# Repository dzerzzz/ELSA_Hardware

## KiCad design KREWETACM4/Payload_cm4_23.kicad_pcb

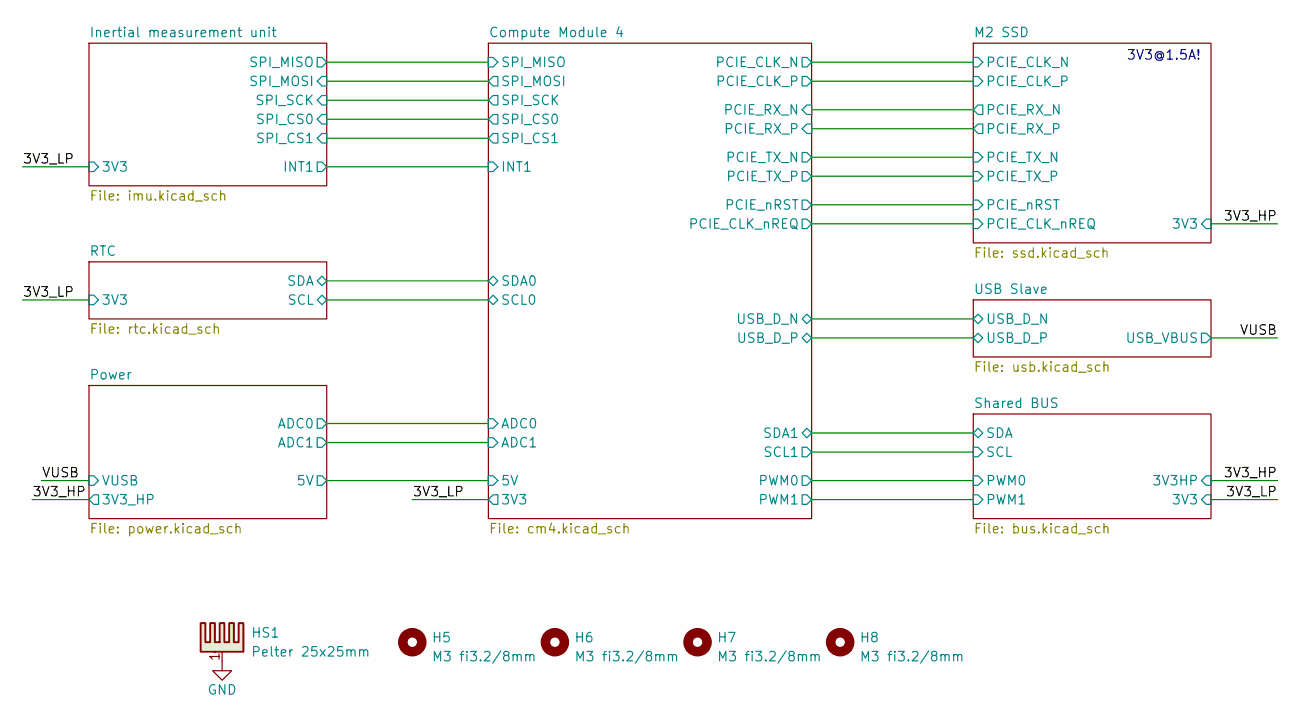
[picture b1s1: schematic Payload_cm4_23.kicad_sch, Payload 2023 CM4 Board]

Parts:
H5, H6, H7, H8: M3 fi3.2/8mm; MountingHole_3.2mm_M3_8mm
HS1: Pelter 25x25mm; Peltier25_25

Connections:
GND: HS1.1; also elsewhere on the board

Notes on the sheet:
3V3@1.5A!

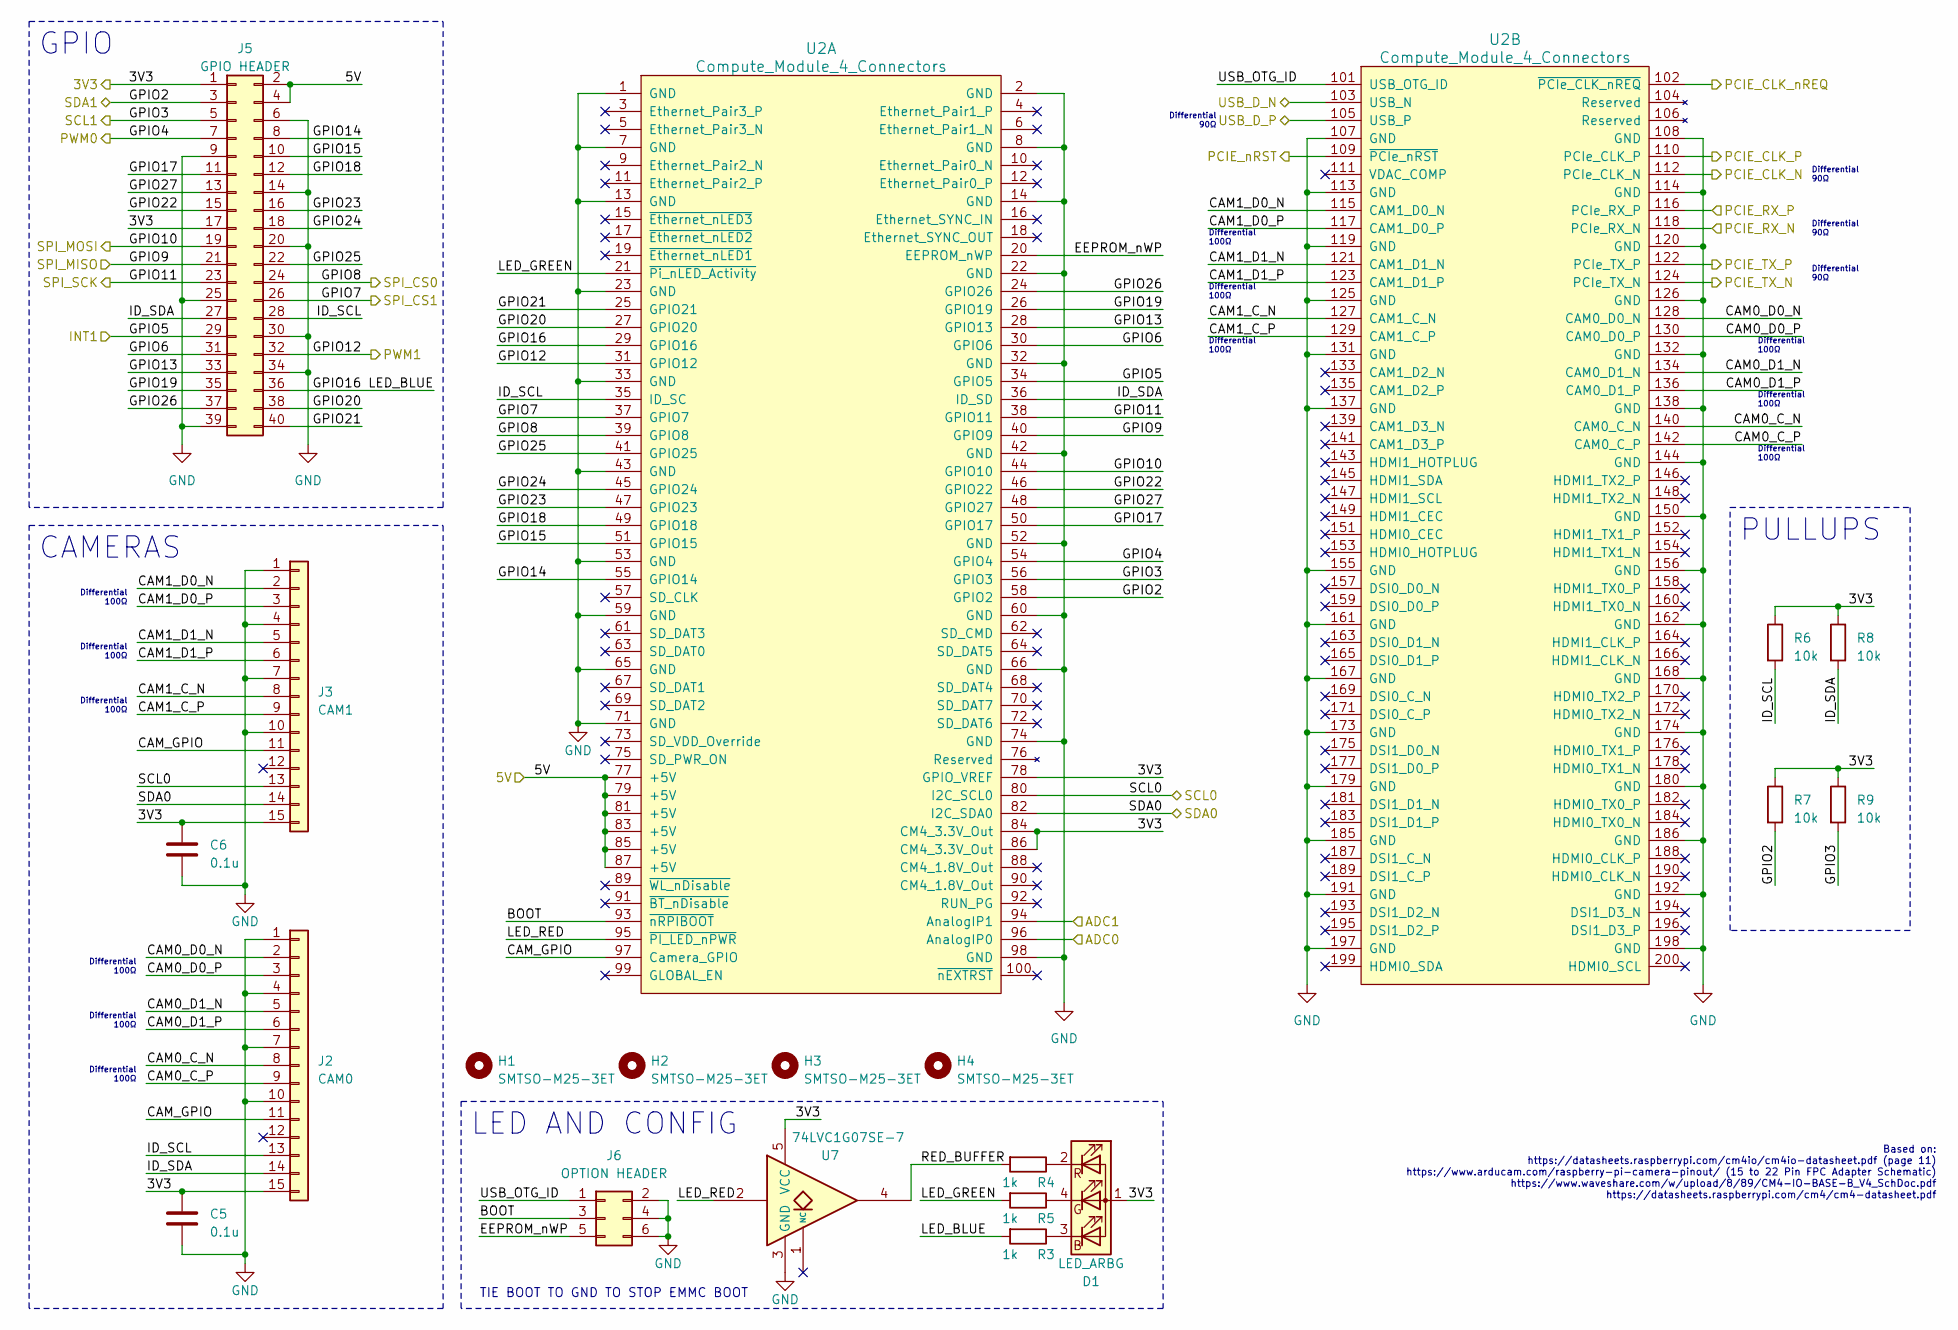
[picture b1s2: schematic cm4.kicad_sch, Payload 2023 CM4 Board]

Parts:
C5, C6: 0.1u; C_0402_1005Metric
D1: LED_ARBG; 150044M155220
H1, H2, H3, H4: SMTSO-M25-3ET; SMTSOM252ET
J2: CAM0; 117342485
J3: CAM1; 117342485
J5: GPIO HEADER; PinHeader_2x20_P2.54mm_Vertical
J6: OPTION HEADER; PinHeader_2x03_P1.27mm_Vertical
R3, R4, R5: 1k; C_0402_1005Metric
R6, R7, R8, R9: 10k; C_0402_1005Metric
U2: Compute_Module_4_Connectors; Raspberry-Pi-4-Compute-Module
U7: 74LVC1G07SE-7; SOT-353_SC-70-5

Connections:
/Compute Module 4/5V: J5.2, J5.4, U2.77 (+5V), U2.79 (+5V), U2.81 (+5V), U2.83 (+5V), U2.85 (+5V), U2.87 (+5V); also elsewhere on the board
/Compute Module 4/ADC0: U2.96 (AnalogIP0); also elsewhere on the board
/Compute Module 4/ADC1: U2.94 (AnalogIP1); also elsewhere on the board
/Compute Module 4/BOOT: J6.3, U2.93 (~nRPIBOOT)
/Compute Module 4/CAM0_C_N: J2.8, U2.140 (CAM0_C_N)
/Compute Module 4/CAM0_C_P: J2.9, U2.142 (CAM0_C_P)
/Compute Module 4/CAM0_D0_N: J2.2, U2.128 (CAM0_D0_N)
/Compute Module 4/CAM0_D0_P: J2.3, U2.130 (CAM0_D0_P)
/Compute Module 4/CAM0_D1_N: J2.5, U2.134 (CAM0_D1_N)
/Compute Module 4/CAM0_D1_P: J2.6, U2.136 (CAM0_D1_P)
/Compute Module 4/CAM1_C_N: J3.8, U2.127 (CAM1_C_N)
/Compute Module 4/CAM1_C_P: J3.9, U2.129 (CAM1_C_P)
/Compute Module 4/CAM1_D0_N: J3.2, U2.115 (CAM1_D0_N)
/Compute Module 4/CAM1_D0_P: J3.3, U2.117 (CAM1_D0_P)
/Compute Module 4/CAM1_D1_N: J3.5, U2.121 (CAM1_D1_N)
/Compute Module 4/CAM1_D1_P: J3.6, U2.123 (CAM1_D1_P)
/Compute Module 4/CAM_GPIO: J2.11, J3.11, U2.97 (Camera_GPIO)
/Compute Module 4/EEPROM_nWP: J6.5, U2.20 (EEPROM_nWP)
/Compute Module 4/GPIO2: J5.3, R7.2, U2.58 (GPIO2); also elsewhere on the board
/Compute Module 4/GPIO4: J5.7, U2.54 (GPIO4); also elsewhere on the board
/Compute Module 4/GPIO5: J5.29, U2.34 (GPIO5); also elsewhere on the board
/Compute Module 4/GPIO6: J5.31, U2.30 (GPIO6)
/Compute Module 4/GPIO7: J5.26, U2.37 (GPIO7); also elsewhere on the board
/Compute Module 4/GPIO8: J5.24, U2.39 (GPIO8); also elsewhere on the board
/Compute Module 4/GPIO9: J5.21, U2.40 (GPIO9); also elsewhere on the board
/Compute Module 4/GPIO10: J5.19, U2.44 (GPIO10); also elsewhere on the board
/Compute Module 4/GPIO11: J5.23, U2.38 (GPIO11); also elsewhere on the board
/Compute Module 4/GPIO12: J5.32, U2.31 (GPIO12); also elsewhere on the board
/Compute Module 4/GPIO13: J5.33, U2.28 (GPIO13)
/Compute Module 4/GPIO14: J5.8, U2.55 (GPIO14)
/Compute Module 4/GPIO15: J5.10, U2.51 (GPIO15)
/Compute Module 4/GPIO16: J5.36, R3.2, U2.29 (GPIO16)
/Compute Module 4/GPIO17: J5.11, U2.50 (GPIO17)
/Compute Module 4/GPIO18: J5.12, U2.49 (GPIO18)
/Compute Module 4/GPIO19: J5.35, U2.26 (GPIO19)
/Compute Module 4/GPIO20: J5.38, U2.27 (GPIO20)
/Compute Module 4/GPIO21: J5.40, U2.25 (GPIO21)
/Compute Module 4/GPIO22: J5.15, U2.46 (GPIO22)
/Compute Module 4/GPIO23: J5.16, U2.47 (GPIO23)
/Compute Module 4/GPIO24: J5.18, U2.45 (GPIO24)
/Compute Module 4/GPIO25: J5.22, U2.41 (GPIO25)
/Compute Module 4/GPIO26: J5.37, U2.24 (GPIO26)
/Compute Module 4/GPIO27: J5.13, U2.48 (GPIO27)
/Compute Module 4/ID_SCL: J2.13, J5.28, R6.2, U2.35 (ID_SC)
/Compute Module 4/ID_SDA: J2.14, J5.27, R8.2, U2.36 (ID_SD)
/Compute Module 4/LED_RED: U2.95 (~PI_LED_nPWR), U7.2
/Compute Module 4/RED_BUFFER: R4.2, U7.4
/Compute Module 4/SCL0: J3.13, U2.80 (I2C_SCL0); also elsewhere on the board
/Compute Module 4/SDA0: J3.14, U2.82 (I2C_SDA0); also elsewhere on the board
/Compute Module 4/USB_OTG_ID: J6.1, U2.101 (USB_OTG_ID)
/M2 SSD/PCIE_CLK_N: U2.112 (PCIe_CLK_N); also elsewhere on the board
/M2 SSD/PCIE_CLK_P: U2.110 (PCIe_CLK_P); also elsewhere on the board
/M2 SSD/PCIE_CLK_nREQ: U2.102 (~PCIe_CLK_nREQ); also elsewhere on the board
/M2 SSD/PCIE_RX_N: U2.118 (PCIe_RX_N); also elsewhere on the board
/M2 SSD/PCIE_RX_P: U2.116 (PCIe_RX_P); also elsewhere on the board
/M2 SSD/PCIE_TX_N: U2.124 (PCIe_TX_N); also elsewhere on the board
/M2 SSD/PCIE_TX_P: U2.122 (PCIe_TX_P); also elsewhere on the board
/M2 SSD/PCIE_nRST: U2.109 (~PCIe_nRST); also elsewhere on the board
/USB Slave/USB_D_N: U2.103 (USB_N); also elsewhere on the board
/USB Slave/USB_D_P: U2.105 (USB_P); also elsewhere on the board
GND: C5.2, C6.2, J2.1, J2.4, J2.7, J2.10, J3.1, J3.4, J3.7, J3.10, J5.6, J5.9, J5.14, J5.20, J5.25, J5.30, J5.34, J5.39, J6.2, J6.4, J6.6, U2.1 (GND), U2.2 (GND), U2.7 (GND), U2.8 (GND), U2.13 (GND), U2.14 (GND), U2.22 (GND), U2.23 (GND), U2.32 (GND), U2.33 (GND), U2.42 (GND), U2.43 (GND), U2.52 (GND), U2.53 (GND), U2.59 (GND), U2.60 (GND), U2.65 (GND), U2.66 (GND), U2.71 (GND), U2.74 (GND), U2.98 (GND), U2.107 (GND), U2.108 (GND), U2.113 (GND), U2.114 (GND), U2.119 (GND), U2.120 (GND), U2.125 (GND), U2.126 (GND), U2.131 (GND), U2.132 (GND), U2.137 (GND), U2.138 (GND), U2.144 (GND), U2.150 (GND), U2.155 (GND), U2.156 (GND), U2.161 (GND), U2.162 (GND), U2.167 (GND), U2.168 (GND), U2.173 (GND), U2.174 (GND), U2.179 (GND), U2.180 (GND), U2.185 (GND), U2.186 (GND), U2.191 (GND), U2.192 (GND), U2.197 (GND), U2.198 (GND), U7.3 (GND); also elsewhere on the board
unnamed: D1.3 (BK), R3.1
unnamed: D1.2 (RK), R4.1

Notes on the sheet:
Differential 100Ω
Differential 90Ω
PULLUPS
TIE BOOT TO GND TO STOP EMMC BOOT
LED AND CONFIG
GPIO
CAMERAS
Based on: https://datasheets.raspberrypi.com/cm4io/cm4io-datasheet.pdf (page 11) https://www.arducam.com/raspberry-pi-camera-pinout/ (15 to 22 Pin FPC Adapter Schematic) https://www.waveshare.com/w/upload/8/89/CM4-IO-BASE-B_V4_SchDoc.pdf https://datasheets.raspberrypi.com/cm4/cm4-datasheet.pdf

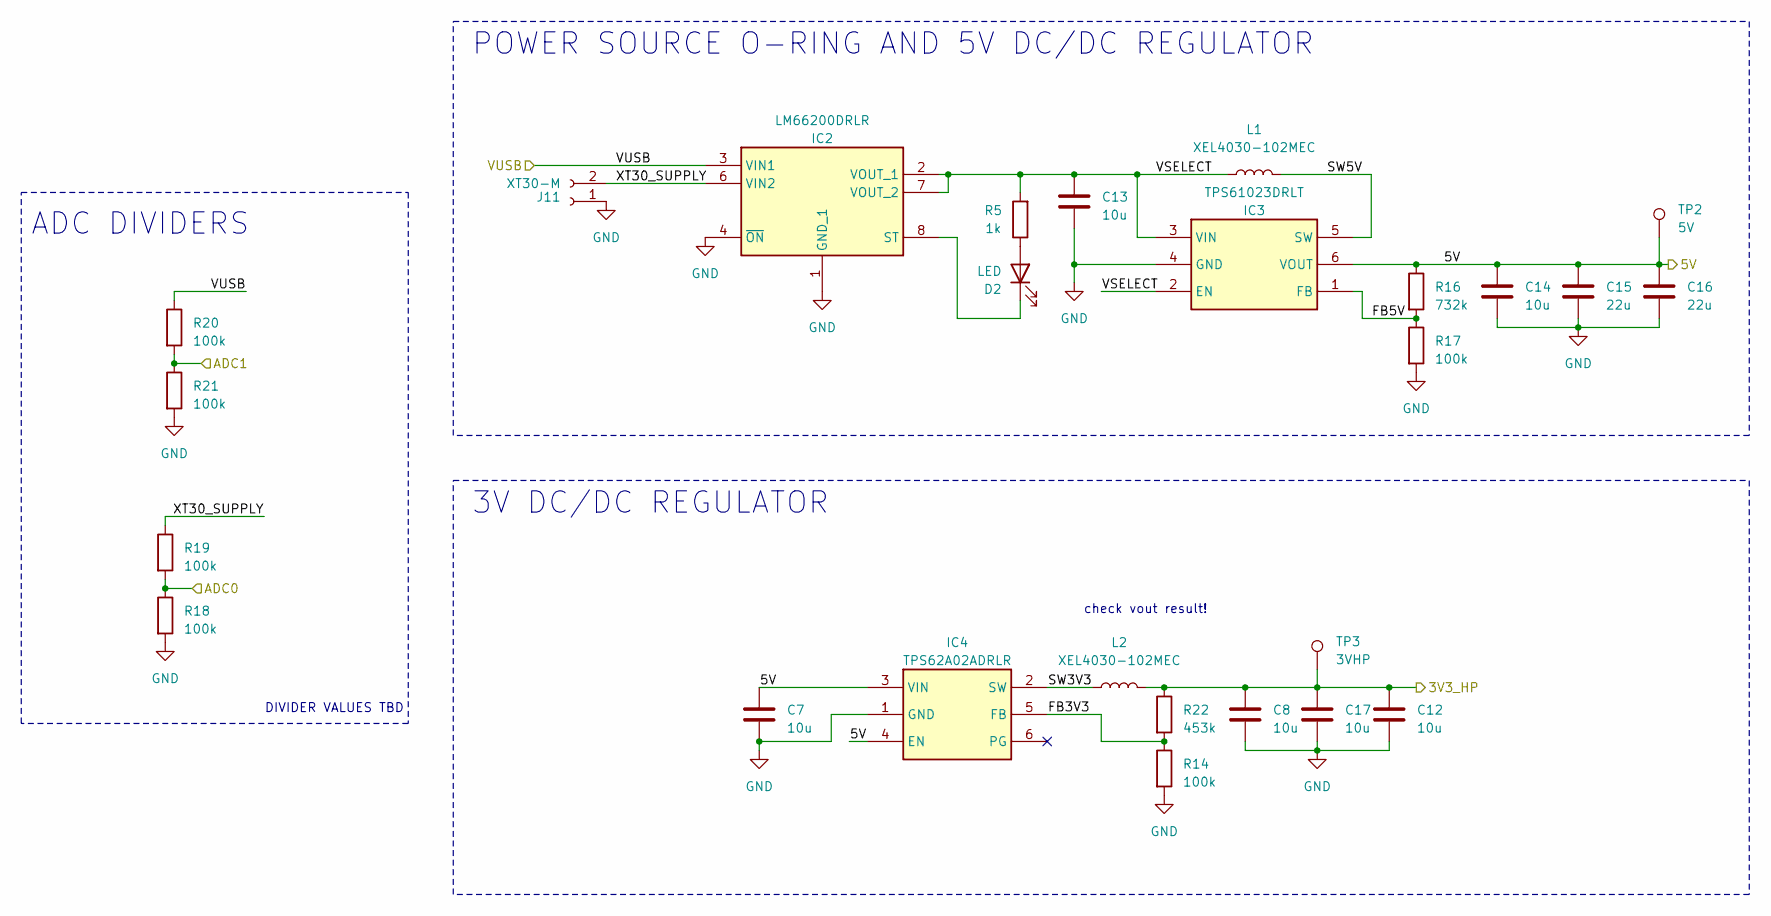
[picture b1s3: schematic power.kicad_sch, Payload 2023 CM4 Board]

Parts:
C7, C8, C12, C13, C14: 10u; C_0805_2012Metric
C15, C16: 22u; C_0805_2012Metric
C17: 10u; C_0402_1005Metric
D2: LED; D_0603_1608Metric
IC2: LM66200DRLR; SOTFL50P160X60-8N; Mouser Part Number 595-LM66200DRLR
IC3: TPS61023DRLT; SOTFL50P160X60-6N; Mouser Part Number 595-TPS61023DRLT
IC4: TPS62A02ADRLR; SOTFL50P160X60-6N; Mouser Part Number 595-TPS62A02ADRLR
J11: XT30-M; AMASS_XT30U-M_1x02_P5.0mm_Vertical
L1, L2: XEL4030-102MEC; L_Coilcraft_XxL4030
R5: 1k; C_0402_1005Metric
R14, R17, R18, R19, R20, R21: 100k; C_0402_1005Metric
R16: 732k; C_0402_1005Metric
R22: 453k; C_0402_1005Metric
TP2: 5V; TestPoint_Pad_D2.0mm
TP3: 3VHP; TestPoint_Pad_D2.0mm

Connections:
/3V3_HP: C8.1, C12.1, C17.1, L2.2, R22.1, TP3.1; also elsewhere on the board
/Compute Module 4/5V: C7.1, C14.1, C15.1, C16.1, IC3.6 (VOUT), IC4.3 (VIN), IC4.4 (EN), R16.1, TP2.1; also elsewhere on the board
/Compute Module 4/ADC0: R18.1, R19.2; also elsewhere on the board
/Compute Module 4/ADC1: R20.2, R21.1; also elsewhere on the board
/Power/FB3V3: IC4.5 (FB), R14.1, R22.2
/Power/FB5V: IC3.1 (FB), R16.2, R17.1
/Power/SW3V3: IC4.2 (SW), L2.1
/Power/SW5V: IC3.5 (SW), L1.2
/Power/XT30_SUPPLY: IC2.6 (VIN2), J11.2, R19.1
/VUSB: IC2.3 (VIN1), R20.1; also elsewhere on the board
GND: C7.2, C8.2, C12.2, C13.2, C14.2, C15.2, C16.2, C17.2, IC2.1 (GND_1), IC2.4 (~ON), IC2.5 (GND_2), IC3.4 (GND), IC4.1 (GND), J11.1, R14.2, R17.2, R18.2, R21.2; also elsewhere on the board
unnamed: D2.1 (K), IC2.8 (ST)

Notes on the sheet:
ADC DIVIDERS
POWER SOURCE O-RING AND 5V DC/DC REGULATOR
check vout result!
3V DC/DC REGULATOR
DIVIDER VALUES TBD

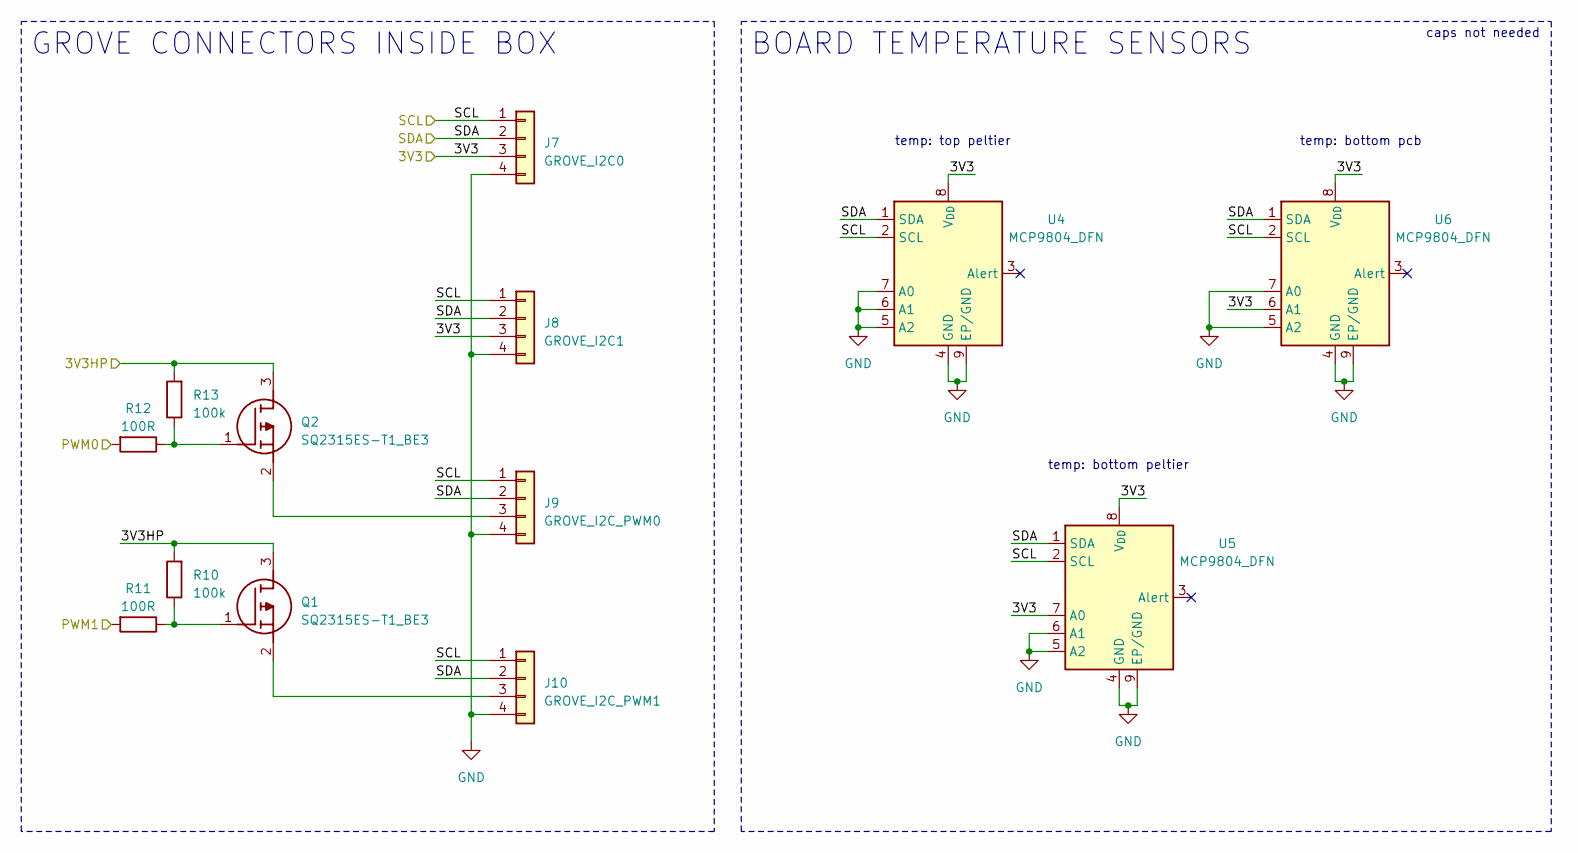
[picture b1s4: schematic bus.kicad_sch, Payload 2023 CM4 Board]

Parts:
J7: GROVE_I2C0; HW4-SMD-2.0
J8: GROVE_I2C1; HW4-SMD-2.0
J9: GROVE_I2C_PWM0; HW4-SMD-2.0
J10: GROVE_I2C_PWM1; HW4-SMD-2.0
Q1, Q2: SQ2315ES-T1_BE3; SOT95P237X112-3N; Mouser Part Number 78-SQ2315ES-T1_BE3
R10, R13: 100k; C_0402_1005Metric
R11, R12: 100R; C_0402_1005Metric
U4, U5, U6: MCP9804_DFN; DFN-8-1EP_3x2mm_P0.5mm_EP1.7x1.4mm

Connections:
/3V3_HP: Q1.3 (D), Q2.3 (D), R10.2, R13.2; also elsewhere on the board
/Compute Module 4/GPIO2: J7.2, J8.2, J9.2, J10.2, U4.1 (SDA), U5.1 (SDA), U6.1 (SDA); also elsewhere on the board
/Compute Module 4/GPIO4: R12.2; also elsewhere on the board
/Compute Module 4/GPIO12: R11.2; also elsewhere on the board
GND: J7.4, J8.4, J9.4, J10.4, U4.4 (GND), U4.5 (A2), U4.6 (A1), U4.7 (A0), U4.9 (EP/GND), U5.4 (GND), U5.5 (A2), U5.6 (A1), U5.9 (EP/GND), U6.4 (GND), U6.5 (A2), U6.7 (A0), U6.9 (EP/GND); also elsewhere on the board
unnamed: J9.3, Q2.2 (S)
unnamed: J10.3, Q1.2 (S)
unnamed: Q1.1 (G), R10.1, R11.1
unnamed: Q2.1 (G), R12.1, R13.1

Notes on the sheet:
temp: bottom pcb
temp: bottom peltier
GROVE CONNECTORS INSIDE BOX
BOARD TEMPERATURE SENSORS
caps not needed
temp: top peltier

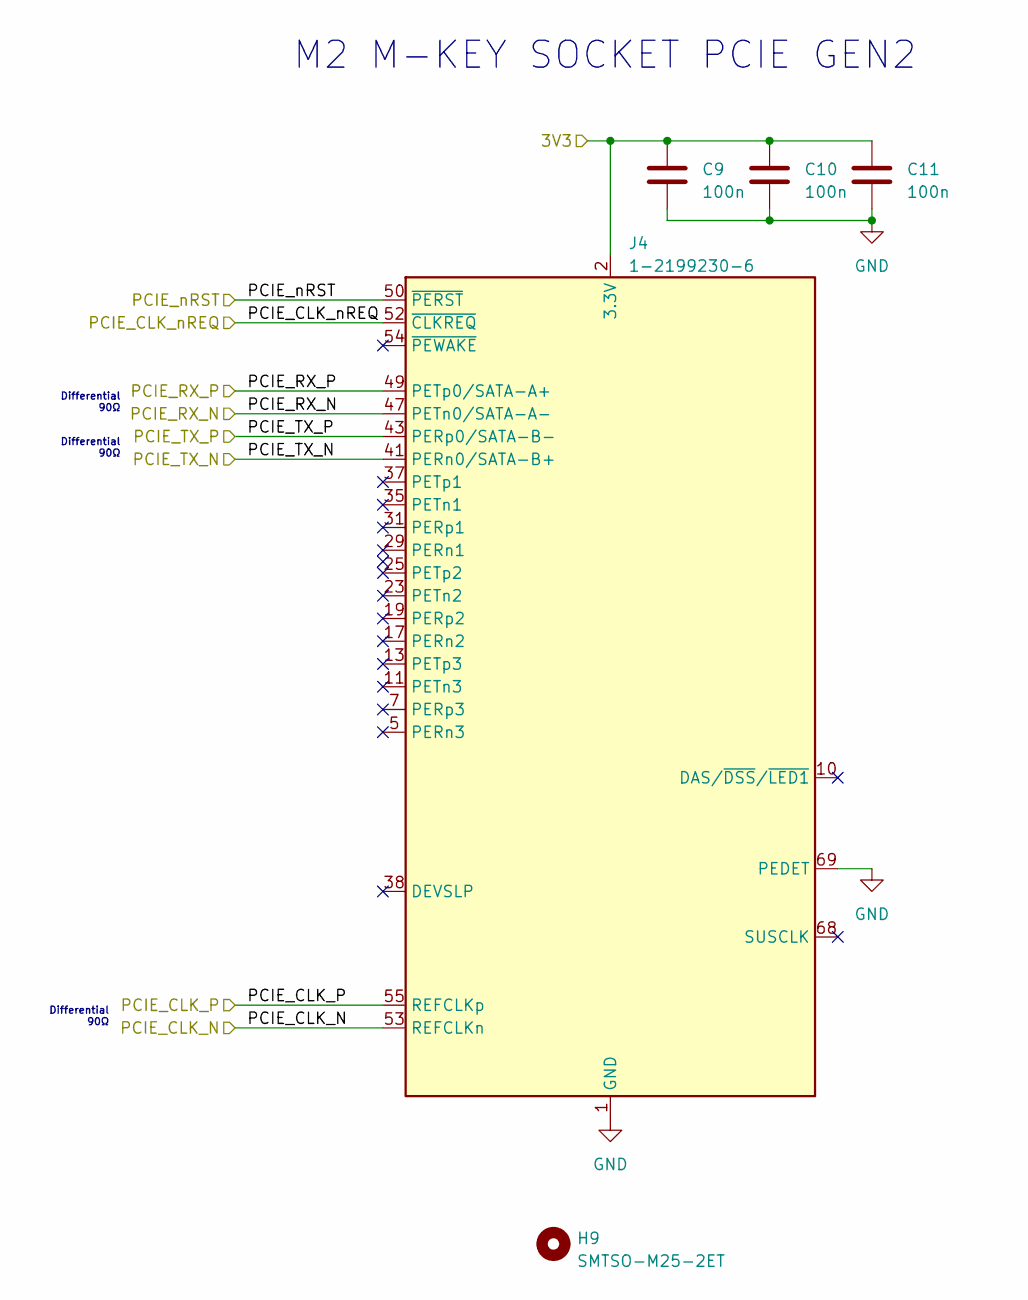
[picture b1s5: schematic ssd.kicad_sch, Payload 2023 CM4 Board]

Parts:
C9, C10, C11: 100n; C_0402_1005Metric
H9: SMTSO-M25-2ET; SMTSOM252ET
J4: 1-2199230-6; 121992306

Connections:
/3V3_HP: C9.1, C10.1, C11.1, J4.2 (3.3V), J4.4 (3.3V), J4.12 (3.3V), J4.14 (3.3V), J4.16 (3.3V), J4.18 (3.3V), J4.70 (3.3V), J4.72 (3.3V), J4.74 (3.3V); also elsewhere on the board
/M2 SSD/PCIE_CLK_N: J4.53 (REFCLKn); also elsewhere on the board
/M2 SSD/PCIE_CLK_P: J4.55 (REFCLKp); also elsewhere on the board
/M2 SSD/PCIE_CLK_nREQ: J4.52 (~CLKREQ); also elsewhere on the board
/M2 SSD/PCIE_RX_N: J4.47 (PETn0/SATA-A-); also elsewhere on the board
/M2 SSD/PCIE_RX_P: J4.49 (PETp0/SATA-A+); also elsewhere on the board
/M2 SSD/PCIE_TX_N: J4.41 (PERn0/SATA-B+); also elsewhere on the board
/M2 SSD/PCIE_TX_P: J4.43 (PERp0/SATA-B-); also elsewhere on the board
/M2 SSD/PCIE_nRST: J4.50 (~PERST); also elsewhere on the board
GND: C9.2, C10.2, C11.2, J4.1 (GND), J4.3 (GND), J4.9 (GND), J4.15 (GND), J4.21 (GND), J4.27 (GND), J4.33 (GND), J4.39 (GND), J4.45 (GND), J4.51 (GND), J4.57 (GND), J4.69 (PEDET), J4.71 (GND), J4.73 (GND), J4.75 (GND); also elsewhere on the board

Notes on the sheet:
Differential 90Ω
M2 M-KEY SOCKET PCIE GEN2

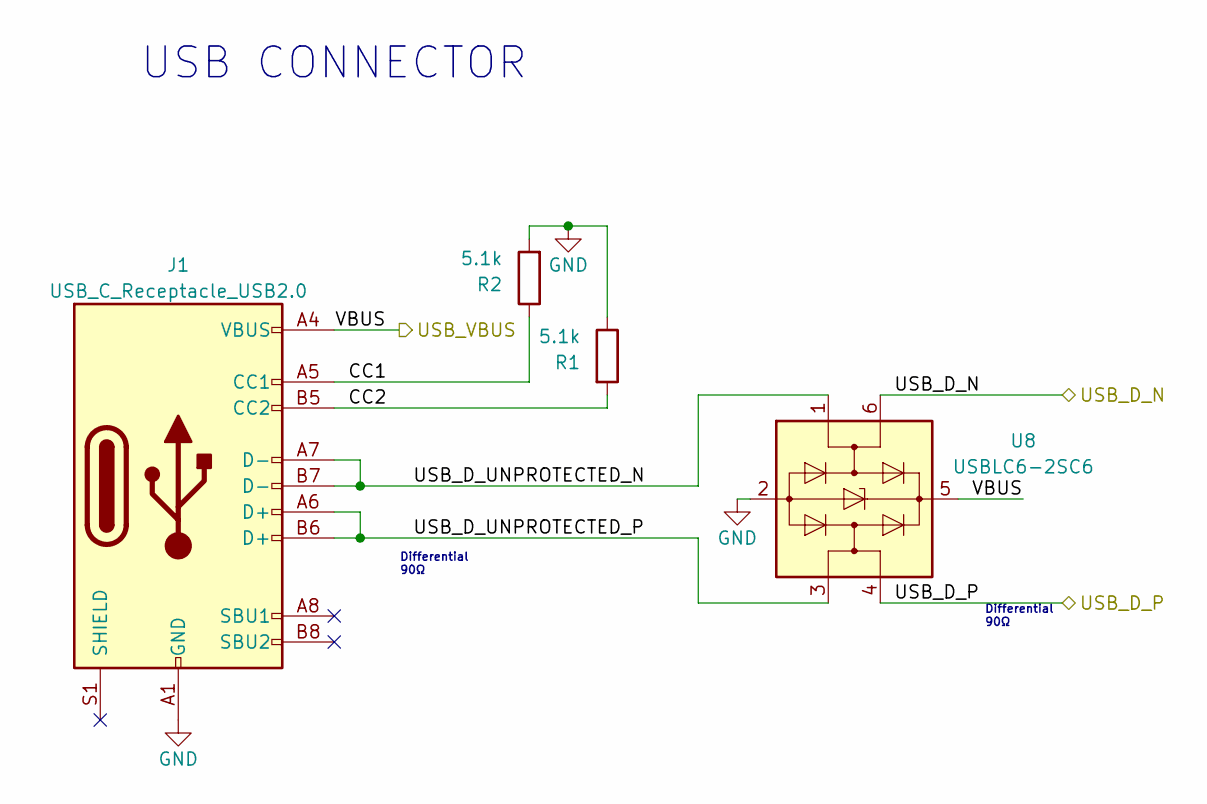
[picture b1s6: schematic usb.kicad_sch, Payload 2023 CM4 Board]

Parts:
J1: USB_C_Receptacle_USB2.0; USB_C_Receptacle_GCT_USB4105-xx-A_16P_TopMnt_Horizontal
R1, R2: 5.1k; C_0402_1005Metric
U8: USBLC6-2SC6; SOT-23-6

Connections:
/USB Slave/CC1: J1.A5 (CC1), R2.1
/USB Slave/CC2: J1.B5 (CC2), R1.2
/USB Slave/USB_D_N: U8.6 (I/O1); also elsewhere on the board
/USB Slave/USB_D_P: U8.4 (I/O2); also elsewhere on the board
/USB Slave/USB_D_UNPROTECTED_N: J1.A7 (D-), J1.B7 (D-), U8.1 (I/O1)
/USB Slave/USB_D_UNPROTECTED_P: J1.A6 (D+), J1.B6 (D+), U8.3 (I/O2)
/VUSB: J1.A4 (VBUS), J1.A9 (VBUS), J1.B4 (VBUS), J1.B9 (VBUS), U8.5 (VBUS); also elsewhere on the board
GND: J1.A1 (GND), J1.A12 (GND), J1.B1 (GND), J1.B12 (GND), R1.1, R2.2, U8.2 (GND); also elsewhere on the board

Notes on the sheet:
USB CONNECTOR
Differential 90Ω

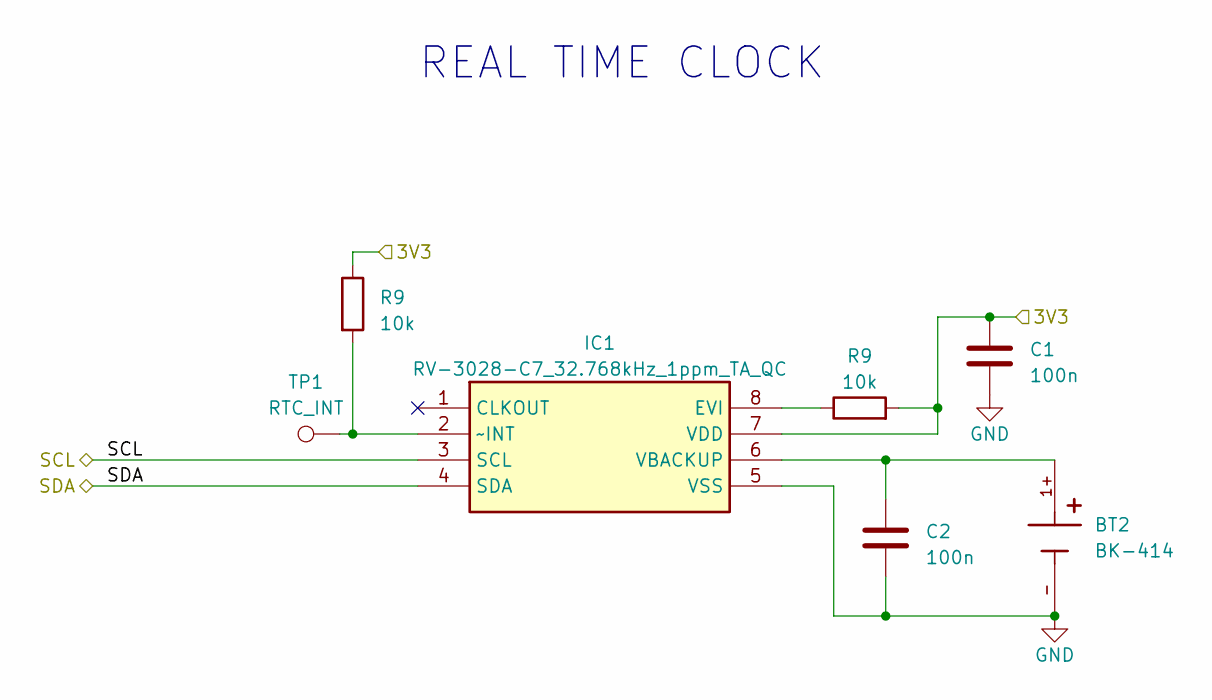
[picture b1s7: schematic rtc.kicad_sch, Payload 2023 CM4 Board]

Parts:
BT2: BK-414; BAT_BK-414; PARTREV D
C1, C2: 100n; C_0402_1005Metric
IC1: RV-3028-C7_32.768kHz_1ppm_TA_QC; RV3028C732768kHz1ppmTAQC; Mouser Part Number 428-203591-MG01
R9: 10k; C_0402_1005Metric
TP1: RTC_INT; TestPoint_Pad_D2.0mm

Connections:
/Compute Module 4/SCL0: IC1.3 (SCL); also elsewhere on the board
/Compute Module 4/SDA0: IC1.4 (SDA); also elsewhere on the board
GND: BT2.-, C1.2, C2.2, IC1.5 (VSS); also elsewhere on the board
unnamed: BT2.1+, C2.1, IC1.6 (VBACKUP)

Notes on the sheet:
REAL TIME CLOCK

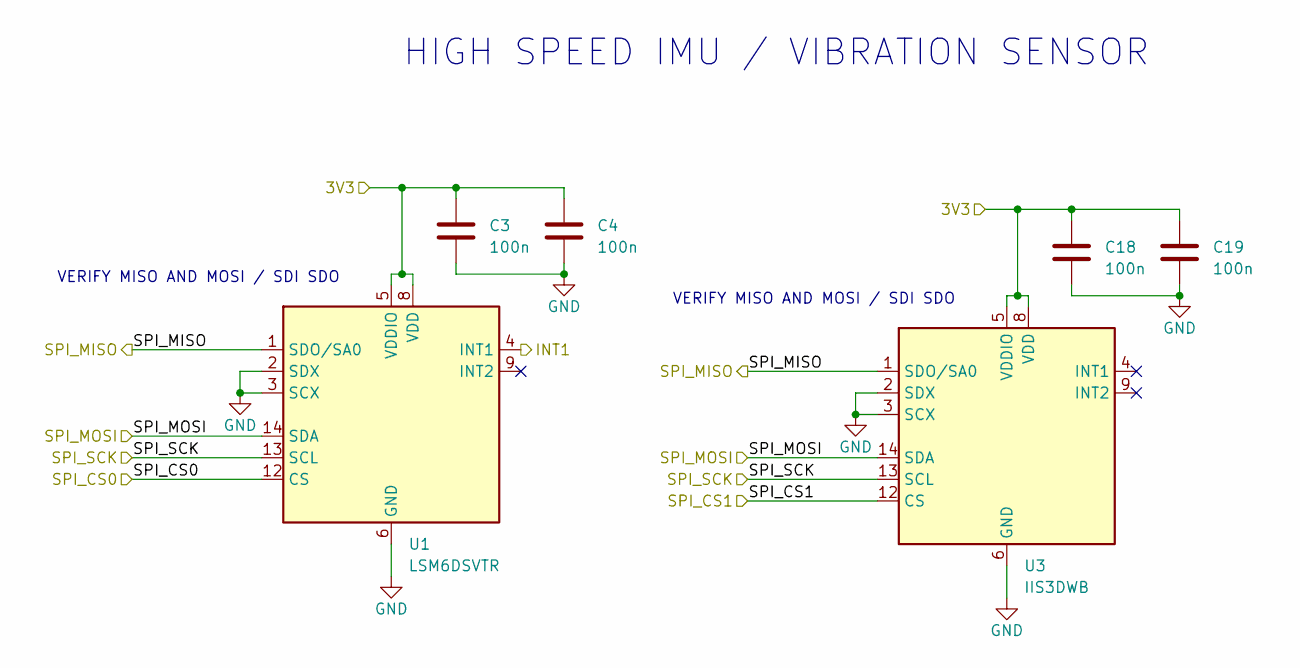
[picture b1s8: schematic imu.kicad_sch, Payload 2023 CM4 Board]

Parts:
C3, C4, C18, C19: 100n; C_0402_1005Metric
U1: LSM6DSVTR; LGA-14_3x2.5mm_P0.5mm_LayoutBorder3x4y
U3: IIS3DWB; LGA-14_3x2.5mm_P0.5mm_LayoutBorder3x4y

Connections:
/Compute Module 4/GPIO5: U1.4 (INT1); also elsewhere on the board
/Compute Module 4/GPIO7: U3.12 (CS); also elsewhere on the board
/Compute Module 4/GPIO8: U1.12 (CS); also elsewhere on the board
/Compute Module 4/GPIO9: U1.1 (SDO/SA0), U3.1 (SDO/SA0); also elsewhere on the board
/Compute Module 4/GPIO10: U1.14 (SDA), U3.14 (SDA); also elsewhere on the board
/Compute Module 4/GPIO11: U1.13 (SCL), U3.13 (SCL); also elsewhere on the board
GND: C3.2, C4.2, C18.2, C19.2, U1.2 (SDX), U1.3 (SCX), U1.6 (GND), U1.7 (GND), U3.2 (SDX), U3.3 (SCX), U3.6 (GND), U3.7 (GND); also elsewhere on the board

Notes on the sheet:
VERIFY MISO AND MOSI / SDI SDO
HIGH SPEED IMU / VIBRATION SENSOR

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
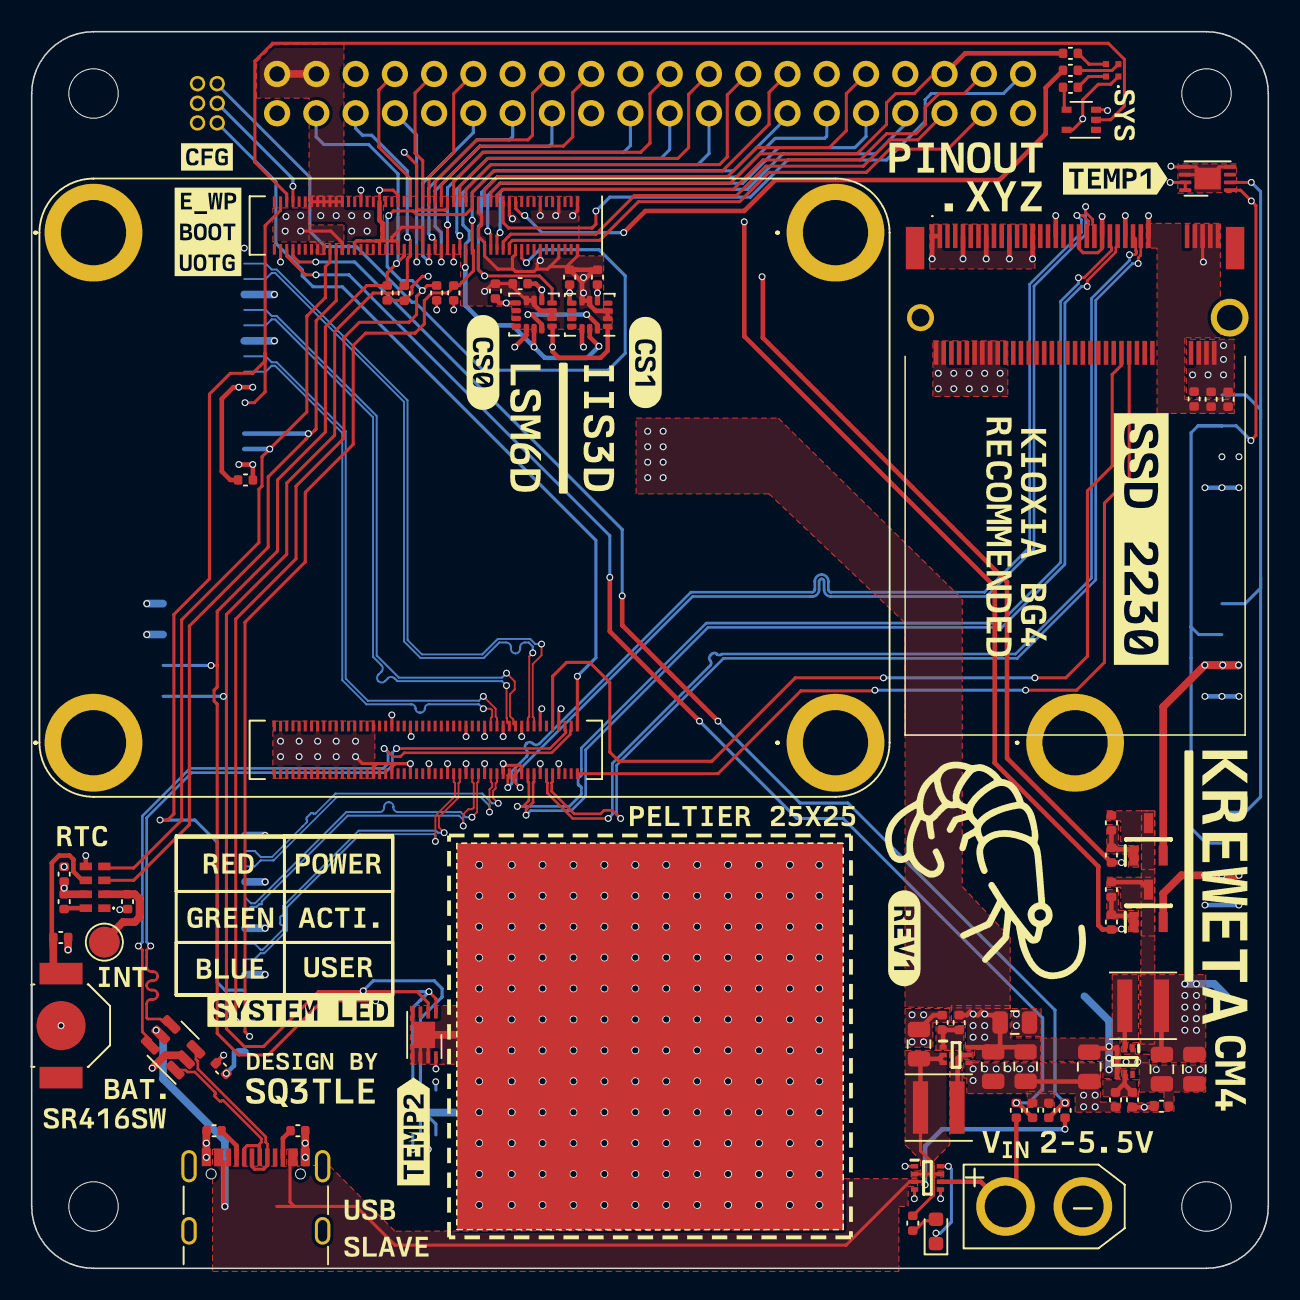
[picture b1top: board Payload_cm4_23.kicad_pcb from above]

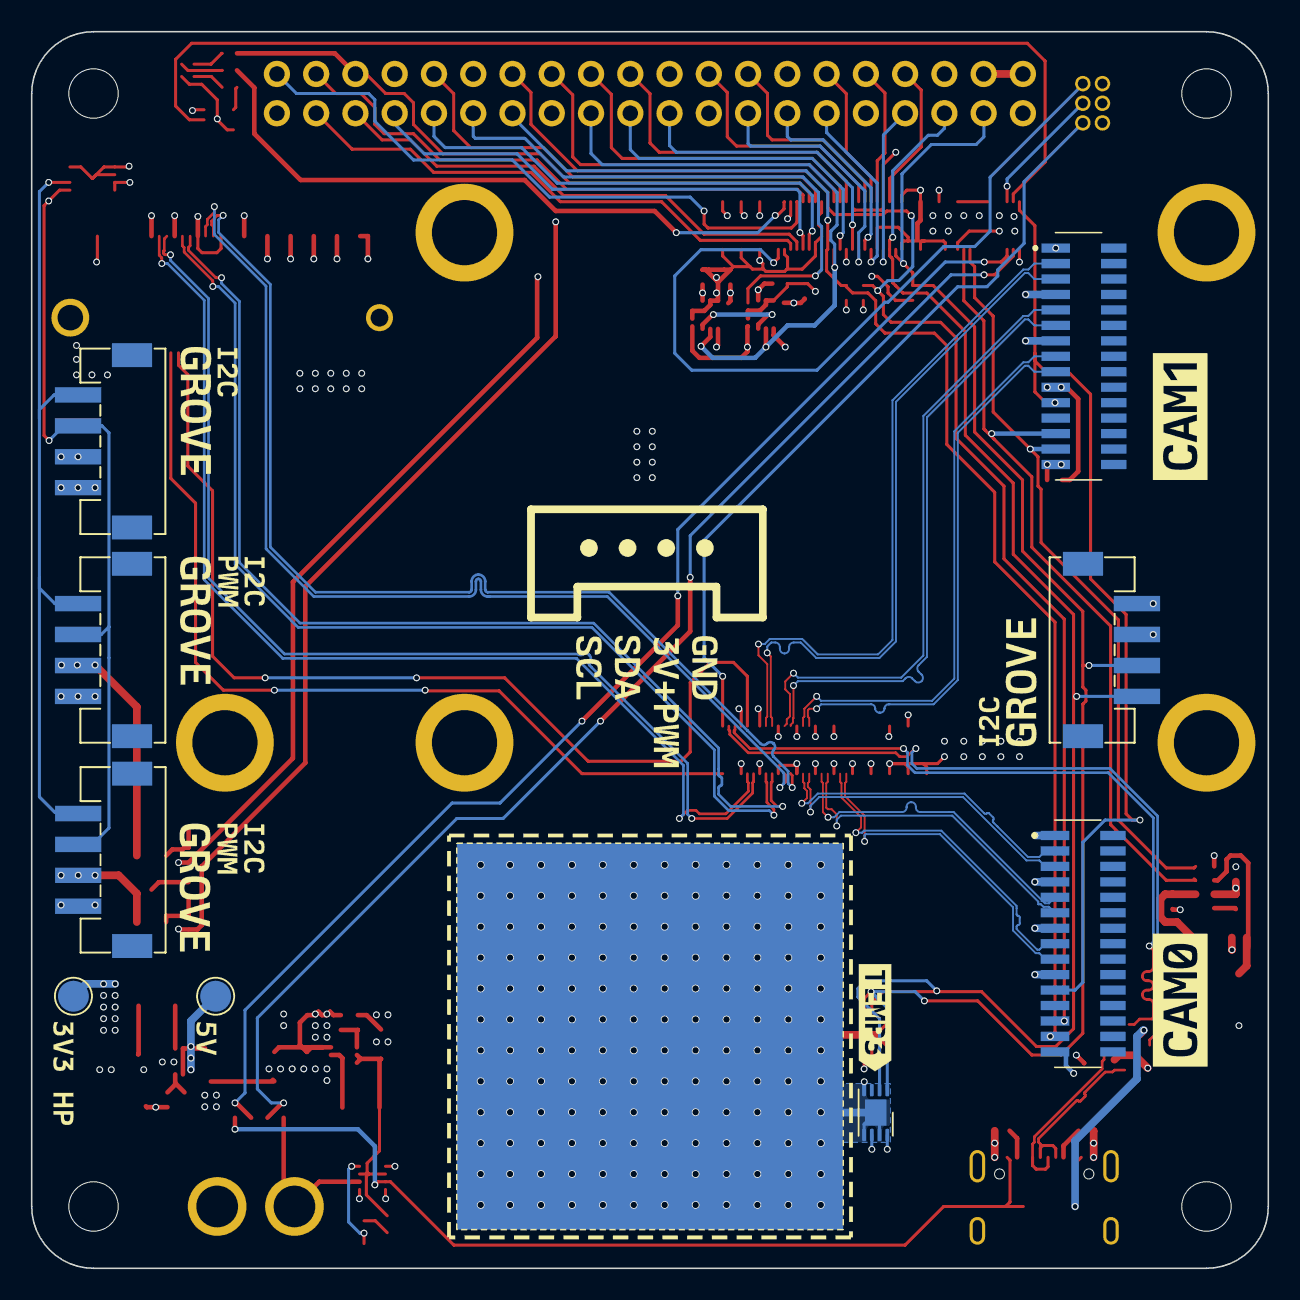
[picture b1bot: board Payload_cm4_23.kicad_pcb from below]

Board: 4 copper layers, 80.0 x 80.0 mm, 139 parts (28 on the bottom side), 88 nets.

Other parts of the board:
R15: 1k; C_0402_1005Metric
R25, R26: 10k; C_0402_1005Metric
kibuzzard-64502B2C: G***; kibuzzard-64502B2C
kibuzzard-64502B8E: G***; kibuzzard-64502B8E
kibuzzard-64502B16: G***; kibuzzard-64502B16
kibuzzard-64502B48: G***; kibuzzard-64502B48
kibuzzard-64502C00: G***; kibuzzard-64502C00
kibuzzard-64502C08: G***; kibuzzard-64502C08
kibuzzard-64502C12: G***; kibuzzard-64502C12
kibuzzard-64502CA6: G***; kibuzzard-64502CA6
kibuzzard-64502D9F: G***; kibuzzard-64502D9F
kibuzzard-64502D76: G***; kibuzzard-64502D76
kibuzzard-64502D82: G***; kibuzzard-64502D82
kibuzzard-64502DA9: G***; kibuzzard-64502DA9
kibuzzard-64502DD2: G***; kibuzzard-64502DD2
kibuzzard-64502DE0: G***; kibuzzard-64502DE0
kibuzzard-64502DF7: G***; kibuzzard-64502DF7
kibuzzard-64502EA4: G***; kibuzzard-64502EA4
kibuzzard-64502EC1: G***; kibuzzard-64502EC1
kibuzzard-64502EDE: G***; kibuzzard-64502EDE
kibuzzard-64503A7D: G***; kibuzzard-64503A7D
kibuzzard-64503B4C: G***; kibuzzard-64503B4C
kibuzzard-64503C4A: G***; kibuzzard-64503C4A
kibuzzard-64503C58: G***; kibuzzard-64503C58
kibuzzard-64503DC6, kibuzzard-64503DC6#2, kibuzzard-64503DC6#3, kibuzzard-64503DC6#4: G***; kibuzzard-64503DC6
kibuzzard-64503DEE, kibuzzard-64503DEE#2: G***; kibuzzard-64503DEE
kibuzzard-64503E35, kibuzzard-64503E35#2, kibuzzard-64503E35#3, kibuzzard-64503E35#4: G***; kibuzzard-64503E35
kibuzzard-64503EF1: G***; kibuzzard-64503EF1
kibuzzard-64503EFE: G***; kibuzzard-64503EFE
kibuzzard-64503F5F: G***; kibuzzard-64503F5F
kibuzzard-64503F69: G***; kibuzzard-64503F69
kibuzzard-645036AE: G***; kibuzzard-645036AE
kibuzzard-645036BA: G***; kibuzzard-645036BA
kibuzzard-645040AD: G***; kibuzzard-645040AD
kibuzzard-645040B5: G***; kibuzzard-645040B5
kibuzzard-645041A0: G***; kibuzzard-645041A0
kibuzzard-645041D0: G***; kibuzzard-645041D0
kibuzzard-645046B1: G***; kibuzzard-645046B1
kibuzzard-645046E4: G***; kibuzzard-645046E4
kibuzzard-645046F2: G***; kibuzzard-645046F2
kibuzzard-6450389A: G***; kibuzzard-6450389A
kibuzzard-6450415A: G***; kibuzzard-6450415A
kibuzzard-64503517: G***; kibuzzard-64503517
kibuzzard-64503613: G***; kibuzzard-64503613
kibuzzard-64503908: G***; kibuzzard-64503908
kibuzzard-64504169: G***; kibuzzard-64504169
kibuzzard-64504227: G***; kibuzzard-64504227
kibuzzard-64504231: G***; kibuzzard-64504231
